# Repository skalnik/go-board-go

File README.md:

# Go board, Go!

An LED based Go board.

## Background

After the frustrations of a normal Go board being knocked around, @sshirokov &
myself started brainstorming how to make a board which is less susceptible to
pieces being knocked around. One of our DJ friends said we should mash it up
with a [Monome](http://monome.org/), and then once I stumbled upon the [4x4 LED
Compatible Button Pad](https://www.sparkfun.com/products/7835) on Sparkfun,
things have taken off from there.

## Firmware Serial API

A basic serial API is available which allows control of the LEDs and alerts when
a button is pressed.

There is a framed protocol to change LED states. Each frame starts with an
`0xAD` constant, followed by the size of the message, then the message itself,
with a checksum at the end.

| Offset  | Description                                                    |
|---------|----------------------------------------------------------------|
| 0x00    | Frame start - constant 0xAD                                    |
| 0x02    | Message length - 0x00-0xFF With the upper bound being unlikely |
| 0x03... | Data. Starting at byte 0x03 and for N bytes                    |
| 0x03+N  | CRC8 Checksum                                                  |

Then treating the `message` part of the frame as

| Offset | Description |
|--------|-------------|
| 0x00   | Operation   |
| 0x01+  | Args        |

The only supported message is Set LED State, which takes the location of the LED
in X then Y coordinates, and then the color value of the LED:

| Value | Description                    |
|-------|--------------------------------|
| 0x01  | Red                            |
| 0x02  | Green                          |
| 0x04  | Blue                           |
| 0x??  | Or the above together for more |

So setting the LED at (5,5) to Red would look something like this:

| Offset  | Value  | Description                                                           |
|---------|--------|-----------------------------------------------------------------------|
| 0x00    | 0xAD   | Start                                                                 |
| 0x01    | 0x04   | Length of message                                                     |
| 0x02    | 0x01   | Set LED State                                                         |
| 0x03    | 0x05   | X position 5                                                          |
| 0x04    | 0x05   | Y position 5                                                          |
| 0x05    | 0x01   | Color value in LSB, 0x01 red, 0x02 green, 0x04 blue (OR for multiple) |
| 0x06    | 0x04   | CRC8 checksum                                                         |

## WIP

This project is still very much work in progress. Updates will happen randomly
as parts arrive and knowledge is gained. This is my first real electronics
project so it may take a while if you're following along. I was just stoked to
get the shift register working:

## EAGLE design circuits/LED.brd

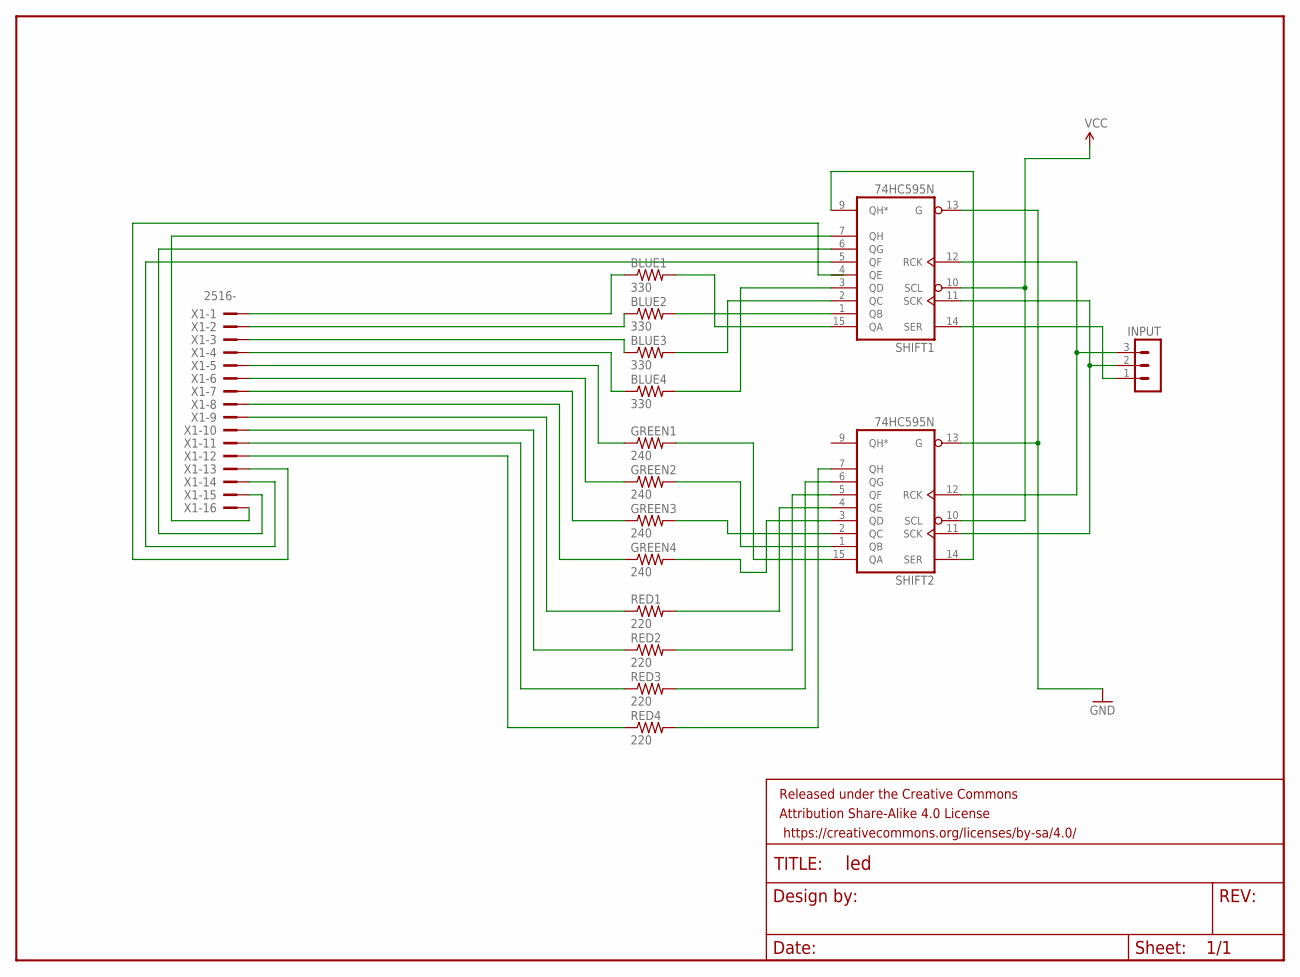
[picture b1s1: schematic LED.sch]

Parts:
BLUE1, BLUE2, BLUE3, BLUE4: 330; AXIAL-0.3EZ
FRAME1: FRAME-LETTER; CREATIVE_COMMONS
GREEN1, GREEN2, GREEN3, GREEN4: 240; AXIAL-0.3EZ
INPUT: MA03-1
RED1, RED2, RED3, RED4: 220; AXIAL-0.3EZ
SHIFT1, SHIFT2: 74HC595N; DIL16
X1: 2516-; PAK100/2500-16

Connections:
GND: SHIFT1.8 (GND), SHIFT1.13 (G), SHIFT2.8 (GND), SHIFT2.13 (G)
unnamed: BLUE4.P$1 (1), X1.4
unnamed: BLUE3.P$1 (1), X1.3
unnamed: BLUE2.P$1 (1), X1.2
unnamed: BLUE1.P$1 (1), X1.1
unnamed: BLUE1.P$2 (2), SHIFT1.15 (QA)
unnamed: BLUE2.P$2 (2), SHIFT1.1 (QB)
unnamed: BLUE3.P$2 (2), SHIFT1.2 (QC)
unnamed: BLUE4.P$2 (2), SHIFT1.3 (QD)
unnamed: SHIFT1.7 (QH), X1.16
unnamed: SHIFT1.6 (QG), X1.15
unnamed: SHIFT1.5 (QF), X1.14
unnamed: GREEN1.P$1 (1), X1.5
unnamed: GREEN2.P$1 (1), X1.6
unnamed: GREEN3.P$1 (1), X1.7
unnamed: GREEN4.P$1 (1), X1.8
unnamed: RED1.P$1 (1), X1.9
unnamed: RED2.P$1 (1), X1.10
unnamed: RED3.P$1 (1), X1.11
unnamed: RED4.P$1 (1), X1.12
unnamed: GREEN1.P$2 (2), SHIFT2.15 (QA)
unnamed: GREEN2.P$2 (2), SHIFT2.1 (QB)
unnamed: GREEN3.P$2 (2), SHIFT2.2 (QC)
unnamed: GREEN4.P$2 (2), SHIFT2.3 (QD)
unnamed: RED1.P$2 (2), SHIFT2.4 (QE)
unnamed: RED2.P$2 (2), SHIFT2.5 (QF)
unnamed: RED3.P$2 (2), SHIFT2.6 (QG)
unnamed: RED4.P$2 (2), SHIFT2.7 (QH)
unnamed: INPUT.3, SHIFT1.12 (RCK), SHIFT2.12 (RCK)
unnamed: INPUT.2, SHIFT1.11 (SCK), SHIFT2.11 (SCK)
unnamed: INPUT.1, SHIFT1.14 (SER)
unnamed: SHIFT1.9 (QH*), SHIFT2.14 (SER)
VCC: SHIFT1.10 (SCL), SHIFT1.16 (VCC), SHIFT2.10 (SCL), SHIFT2.16 (VCC)

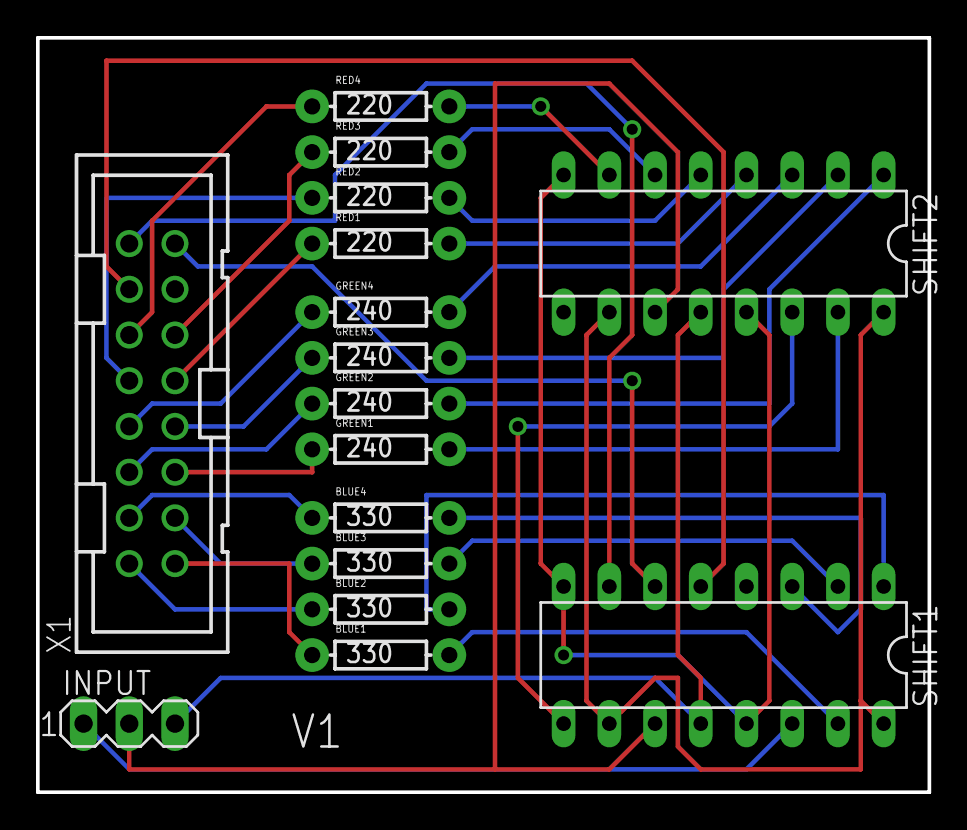
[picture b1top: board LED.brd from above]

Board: 2 copper layers, 49.5 x 41.9 mm, 17 parts (0 on the bottom side), 33 nets.

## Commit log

2014-02-11 Add initial reference links :link:
2014-02-11 Add breakout board links :cactus:
2014-02-11 Add a README :eyeglasses:
2014-02-11 This is how much of a noob I am :1234:
2014-02-11 Of course I fuck up the image link :art:
2014-02-14 Add LED grid test firmware :black_square_button:
2014-02-14 Ignore ino build dir :x:
2014-02-14 Lets see if we wired the shift reg properly :link:
2014-02-14 Add basic serial control firmware :wrench:
2014-02-16 Thoughts about how the serial API will look :eyes:
2014-02-16 Write initial Serial API firmware :rocket:
2014-02-16 Hey, you! Get on the next line :point_down:
2014-02-16 Adjust some output :speech_balloon:
2014-02-17 Good ol' off by one errors :one:
2014-02-19 Steal @sshirokov's protocol :dash:
2014-02-19 Update formating & wording :abcd:
2014-02-26 Add eagle project :bird:
2014-02-27 Fix schematic & lay out board
2014-03-04 Fix resistor order, add copper pour & version
2014-03-19 Start up the Bill of Materials :clipboard:

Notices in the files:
parts and their libraries:
SparkFun-Aesthetics: Licensing: Creative Commons ShareAlike 4.0 International - https://creativecommons.org/licenses/by-sa/4.0
SparkFun-Aesthetics: Released under the Creative Commons Attribution Share-Alike 4.0 License
SparkFun-Aesthetics: https://creativecommons.org/licenses/by-sa/4.0
